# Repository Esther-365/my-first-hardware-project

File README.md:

# my-first-hardware-project
**Pet Starbie** 
The Pet Starbie is a small electronic pet I'm designing the idea is from the Tamagotchi device.
I used the Starbie project by [SharKingStudios as my starting point](https://github.com/SharKingStudios/Starbie/blob/main/Week%201%20Guide.md), but I added a few features of my own. I designed the circuit and PCB using KiCad. The controller I used is the XIAO ESP32-C3, and I'm using Arduino IDE to work on the firmware. I designed a custom copper electrode for the touch sensor and added voltage dividers for battery monitoring and USB detection.

**Features**
•	An OLED display to show the pet and its animations.
•	An MPU6050 to detect movement and shaking.
•	Two buttons for interacting with the pet.
•	A DHT11 to measure temperature and moisture.
•	A capacitive touch sensor so the pet can react to being touched.
•	Battery voltage monitoring so the pet can react when the battery is low.
•	USB power detection so the pet can have a different expression when plugged in.

# 3D View of PCB

[**Onshape Project Link**](https://cad.onshape.com/documents/30b1cbdd64f530785b53ed5e/w/46caed9ad191264a28cf3bcb/e/df15983b73c9392080d00bbe?renderMode=0&uiState=6add6acb7146cb9c66f35473)
# PCB Enclosure

## Controls

| Control | Function |
|---------|----------|
| Button 1 | First press opens the radial menu. Second press selects the highlighted action. |
| Button 2 | Shows or hides the stats screen. |
| Tilt | While the menu is open, tilt Starbie to move the selector ball to an action. |
| Shake | Shake Starbie to trigger a reaction. |
| Touch | Pet Starbie's head. It jumps, shows hearts, and gets happier. |
| USB-detect | Shows a happy face when plugged in |

# BOM Table
## Bill of Materials (BOM)

| Part | Qty | Unit Price ($) | Vendor |
|---|---:|---:|---|
| 10nF Capacitor | 10 | 0.10 | [DigiKey](https://www.digikey.com/en/products/detail/samsung-electro-mechanics/CL21B103KBANNNC/3886673) |
| 100nF Capacitor | 10 | 0.70 | [DigiKey](https://www.digikey.com/en/products/detail/kemet/C0805F104K5RAC3020/12082500) |
| 0.96 OLED | 4 | 5.99 | [Amazon](https://www.amazon.com/dp/B0GBVWBWCR) |
| MPU6050 | 1 | 6.99 | [Amazon](https://www.amazon.com/dp/B01DK83ZYQ) |
| JST-PH | 10 | 0.10 | [Newark](https://www.newark.com/jst-japan-solderless-terminals/b2b-ph-k-s-lf-sn/header-top-entry-2way-2mm/dp/37K9940) |
| 10k Resistor | 2 | 4.97 | [Amazon](https://www.amazon.com/dp/B0B4JFPHTW) |
| MX Switches | 6 | 0.18 | [Amazon](https://www.amazon.com/dp/B0FQP8VYX4) |
| XIAO ESP32-C3-SMD | 1 | 4.99 | [Seeed Studio](https://www.seeedstudio.com/Seeed-XIAO-ESP32C3-p-5431.html) |
| DHT11 | 1 | 5.99 | [Amazon](https://www.amazon.com/dp/B09TKTZMSL) |
| AT42QT1011-TSHR | 1 | 0.77 | [DigiKey](https://www.digikey.com/en/products/detail/microchip-technology/AT42QT1011-TSHR/2268868) |
| Key Caps | 1 | 11.99 | [Amazon](https://www.amazon.com/dp/B0CQ2XG16M) |
| PCB | 1 | 10.00 | [JLCPCB](https://www.jlcpcb.com/) |
| 200k Resistor | 10 | 0.10 | [DigiKey](https://www.digikey.com/en/products/detail/yageo/AC0805FR-07200KL/6006555) |
| 100k Resistor | 10 | 0.15 | [DigiKey](https://www.digikey.com/en/products/detail/yageo/RE0805FRE07100KL/5923482) |
| 150k Resistor | 10 | 0.15 | [DigiKey](https://www.digikey.com/en/products/detail/yageo/RE0805FRE07150KL/5923504) |
| 1000mAh Battery | 1 | 7.99 | [eBay](https://www.ebay.com/itm/174819689504) |
| M2.5 Hardware | 1 | 9.99 | [Amazon](https://www.amazon.com/dp/B0FG2BYJSR) |
| M3 Hardware | 1 | 8.99 | [Amazon](https://www.amazon.com/dp/B0G11HFYMX) |
| Fabric-over-Foam Gasket | 1 | 16.55 | [Newark](https://www.newark.com/wurth-elektronik/3021008/shielding-gasket-square-1-metre/dp/58T7176) |
| 40-pin Female Header Strip | 1 | 1.95 | [SparkFun](https://www.sparkfun.com/straight-header-female-pth-0-1in-40-pin.html) |

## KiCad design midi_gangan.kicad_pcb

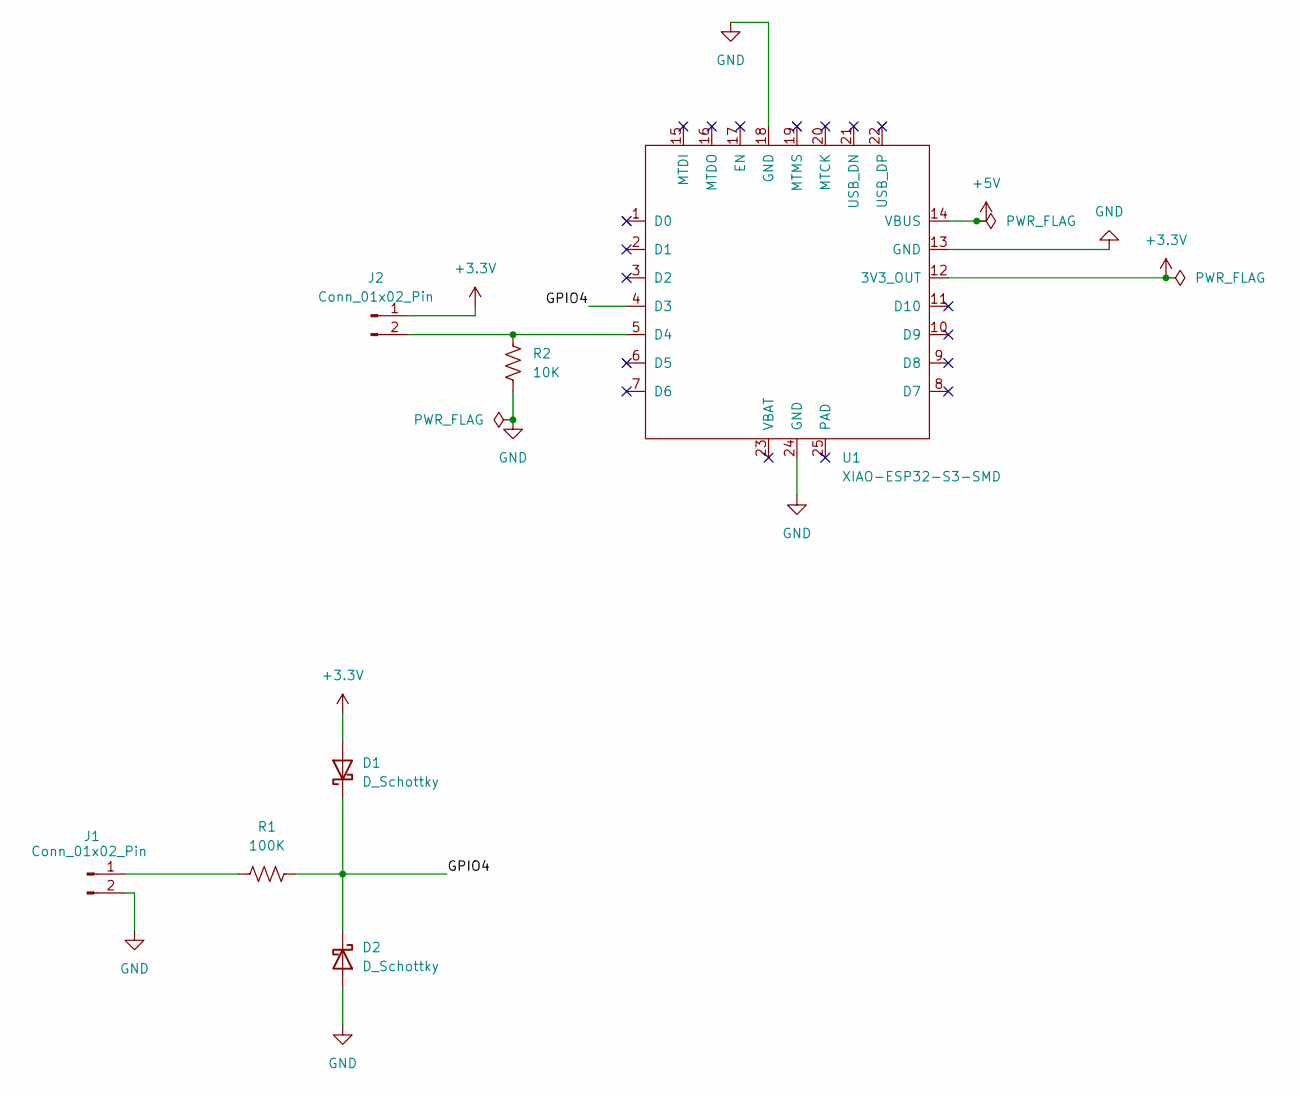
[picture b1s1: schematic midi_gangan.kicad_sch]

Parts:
D1, D2: D_Schottky; D_SOD-123F
J1, J2: Conn_01x02_Pin; TerminalBlock_Phoenix_MKDS-1,5-2_1x02_P5.00mm_Horizontal
R1: 100K; R_0805_2012Metric
R2: 10K; R_0805_2012Metric
U1: XIAO-ESP32-S3-SMD

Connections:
+3.3V: D1.2 (A), J2.1, U1.12 (3V3_OUT)
+5V: U1.14 (VBUS)
/GPIO4: D1.1 (K), D2.1 (K), R1.2, U1.4 (D3)
GND: D2.2 (A), J1.2, R2.2, U1.13 (GND), U1.18 (GND), U1.24 (GND)
unnamed: J1.1, R1.1
unnamed: J2.2, R2.1, U1.5 (D4)

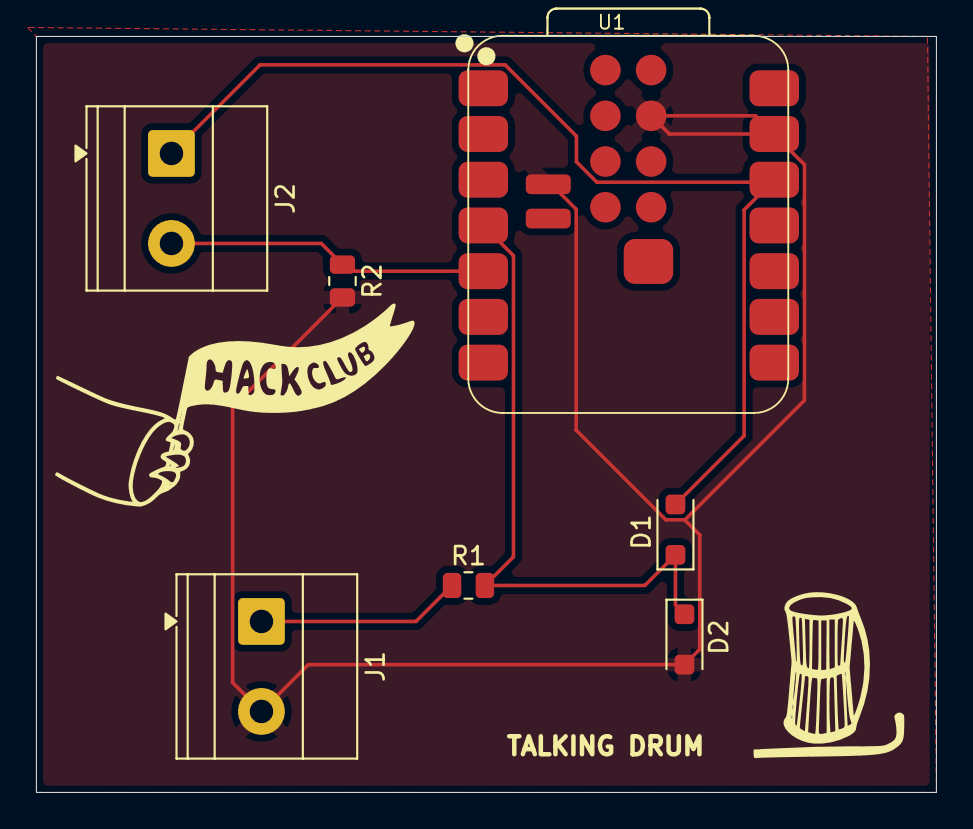
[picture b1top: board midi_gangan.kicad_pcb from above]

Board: 2 copper layers, 50.0 x 42.0 mm, 7 parts (0 on the bottom side), 5 nets.

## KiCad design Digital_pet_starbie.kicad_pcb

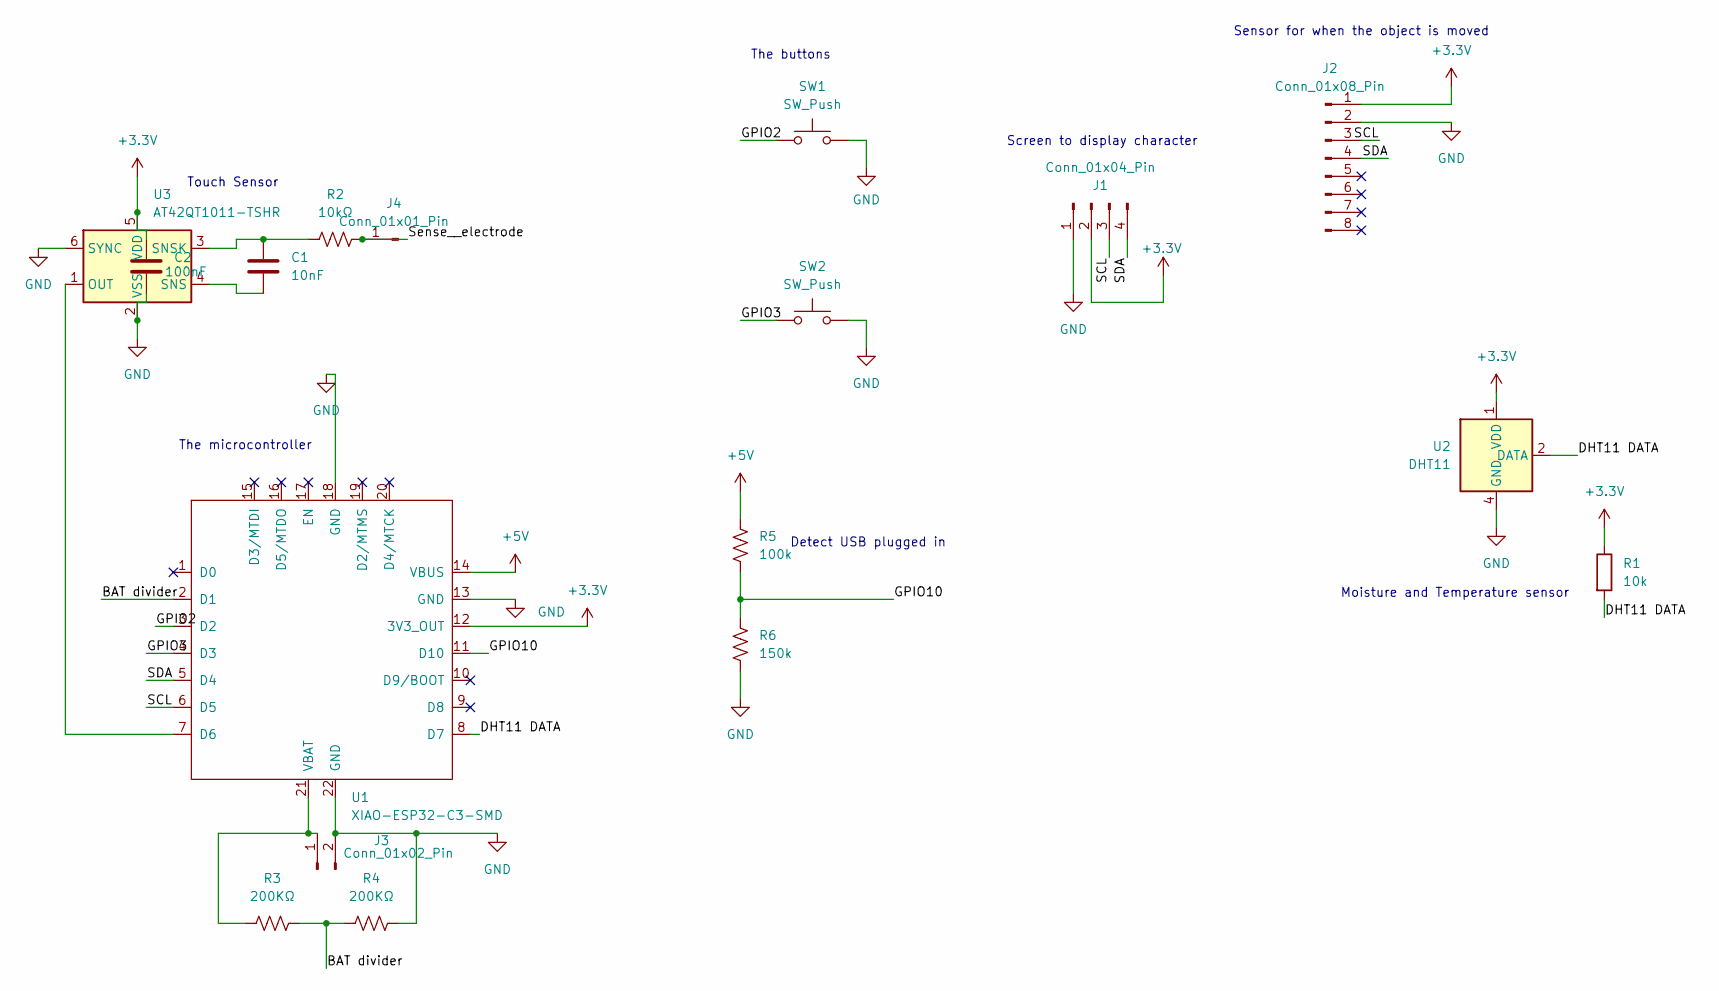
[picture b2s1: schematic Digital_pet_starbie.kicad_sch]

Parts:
C1: 10nF; C_0805_2012Metric_Pad1.18x1.45mm_HandSolder
C2: 100nF; C_0805_2012Metric_Pad1.18x1.45mm_HandSolder
J1: Conn_01x04_Pin; Display_128x64_096_I2C
J2: Conn_01x08_Pin; PinHeader_1x08_P2.54mm_Vertical
J3: Conn_01x02_Pin; JST_PH_B2B-PH-K_1x02_P2.00mm_Vertical
J4: Conn_01x01_Pin; Touch_electrode
R1: 10k; R_Axial_DIN0204_L3.6mm_D1.6mm_P7.62mm_Horizontal
R2: 10kΩ; R_0805_2012Metric_Pad1.20x1.40mm_HandSolder
R3, R4: 200KΩ; R_0805_2012Metric_Pad1.20x1.40mm_HandSolder
R5: 100k; R_0805_2012Metric_Pad1.20x1.40mm_HandSolder
R6: 150k; R_0805_2012Metric_Pad1.20x1.40mm_HandSolder
SW1, SW2: SW_Push; SW_Cherry_MX_1.00u_PCB
U1: XIAO-ESP32-C3-SMD
U2: DHT11; Aosong_DHT11_5.5x12.0_P2.54mm
U3: AT42QT1011-TSHR; SOT-23-6_Handsoldering

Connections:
+3.3V: C2.1, J1.2, J2.1, R1.1, U1.12 (3V3_OUT), U2.1 (VDD), U3.5 (VDD)
+5V: R5.2, U1.14 (VBUS)
/BAT divider: R3.2, R4.1, U1.2 (D1)
/DHT11 DATA: R1.2, U1.8 (D7), U2.2 (DATA)
/GPIO2: SW1.1, U1.3 (D2)
/GPIO3: SW2.1, U1.4 (D3)
/GPIO10: R5.1, R6.2, U1.11 (D10)
/SCL: J1.3, J2.3, U1.6 (D5)
/SDA: J1.4, J2.4, U1.5 (D4)
/Sense__electrode: J4.1 (Pin_1_1), R2.2
GND: C2.2, J1.1, J2.2, J3.2, R4.2, R6.1, SW1.2, SW2.2, U1.13 (GND), U1.18 (GND), U1.22 (GND), U2.4 (GND), U3.2 (VSS), U3.6 (SYNC)
unnamed: J3.1, R3.1, U1.21 (VBAT)
unnamed: U1.7 (D6), U3.1 (OUT)
unnamed: C1.2, U3.4 (SNS)
unnamed: C1.1, R2.1, U3.3 (SNSK)

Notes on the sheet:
The buttons
The microcontroller
Screen to display character
Sensor for when the object is moved
Moisture and Temperature sensor
Touch Sensor
Detect USB plugged in

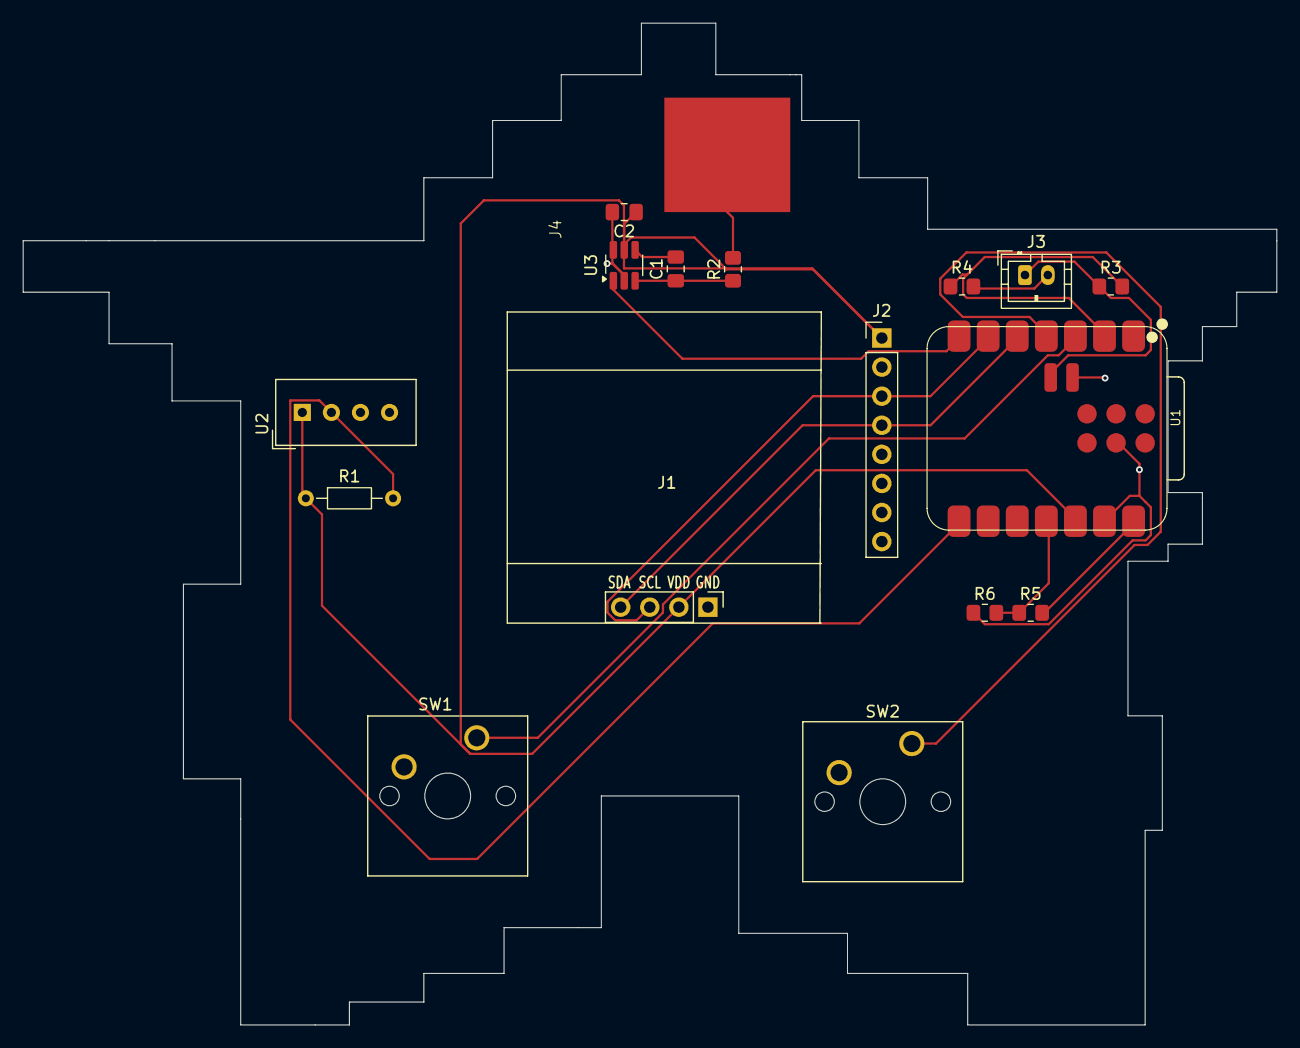
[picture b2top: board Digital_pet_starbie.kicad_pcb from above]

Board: 2 copper layers, 109.5 x 87.5 mm, 17 parts (0 on the bottom side), 15 nets.
